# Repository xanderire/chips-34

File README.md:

# chips-34

Prototype, diodless pcb with minor key stagger and two thumb keys.

This started as a project to learn [Ergogen](https://github.com/ergogen/ergogen) and [KiCad](https://www.kicad.org/)

- Work-in-progress pcb that is under **100mm x 100mm** in order to facilitate a common discounted price for pcb manufactures for small pcbs.
- I do not claim this to be the most efficent or best way to build a keyboard pcb.
- This project is more to have fun and prototype different designs.
- As such I also cannot promise any files in this repo are correct and will work as production files.

---

## BOM

| Components                                              | Amount |
| :------------------------------------------------------ | :----: |
| Arduino Pro Micro                                       | 2      |
| TRRS-PJ-320A-dual                                       | 2      |
| SPST Tactile Switch                                     | 2      |
| Kailh MX Hotswap Sockets                                | 34     |
| MX Switches                                             | 34     |
| MX Keycaps                                              | 34     |

---

## Images

[(Back to top)](#chips-34)

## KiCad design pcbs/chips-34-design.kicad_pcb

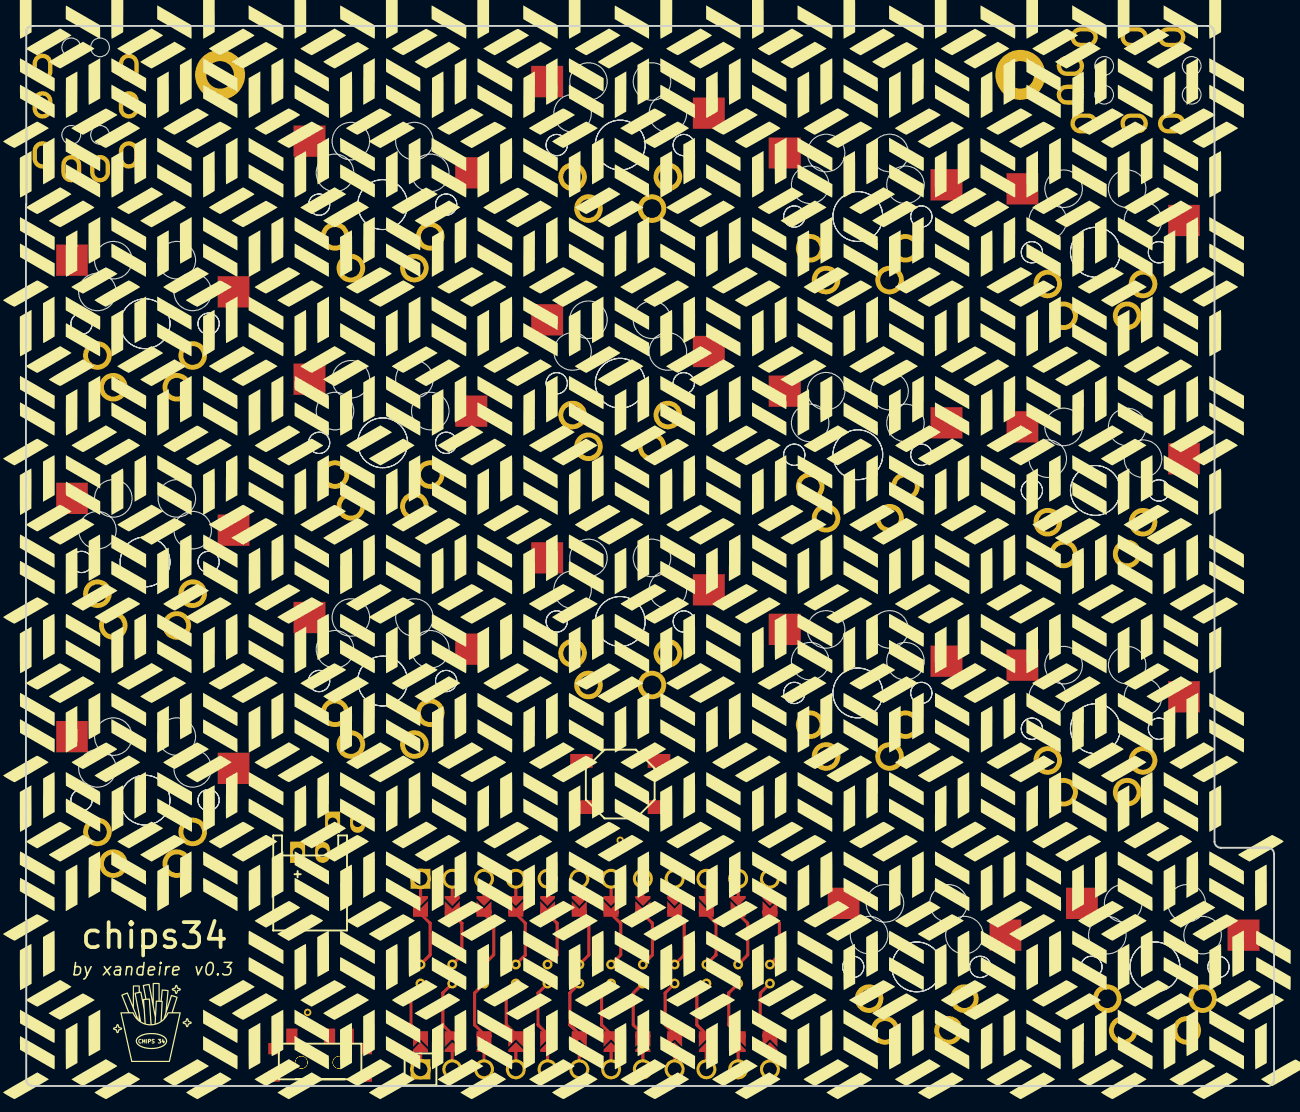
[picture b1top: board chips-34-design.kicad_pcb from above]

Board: 2 copper layers, 99.8 x 84.8 mm, 43 parts (0 on the bottom side), 23 nets, no tracks yet.

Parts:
B1, B2: SW_TACT_ALPS_SKQGABE010
JST1, JST2: JST_PH_S2B-PH-K_02x2.00mm_Angled
MCU1: ProMicro
S1, S2, S3, S4, S5, S6, S7, S8, S9, S10, S11, S12, S13, S14, S15, S16, S17, S18, S19, S20, S21, S22, S23, S24, S25, S26, S27, S28, S29, S30, S31, S32, S33, S34: MX
T1, T2: SPDT_C128955
TRRS1, TRRS2: TRRS-PJ-320A-dual

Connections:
BAT: JST1.1, JST2.1, T1.2, T2.2
GND: B1.2, B2.2, JST1.2, JST2.2, MCU1.2, MCU1.21, MCU1.22, S1.1, S2.1, S3.1, S4.1, S5.1, S6.1, S7.1, S8.1, S9.1, S10.1, S11.1, S12.1, S13.1, S14.1, S15.1, S16.1, S17.1, S18.1, S19.1, S20.1, S21.1, S22.1, S23.1, S24.1, S25.1, S26.1, S27.1, S28.1, S29.1, S30.1, S31.1, S32.1, S33.1, S34.1, TRRS1.1, TRRS1.2, TRRS2.1, TRRS2.2
P1: TRRS1.3, TRRS2.3
RAW: MCU1.1, T1.1, T2.1
RST: B1.1, B2.1, MCU1.3
VCC: MCU1.4, TRRS1.4, TRRS2.4
matrix_index_bottom: MCU1.16, S10.2, S27.2
matrix_index_home: MCU1.9, S11.2, S28.2
matrix_index_top: MCU1.8, S12.2, S29.2
matrix_inner_bottom: MCU1.14, S13.2, S30.2
matrix_inner_home: MCU1.15, S14.2, S31.2
matrix_inner_top: MCU1.10, S15.2, S32.2
matrix_middle_bottom: MCU1.17, S7.2, S24.2
matrix_middle_home: MCU1.7, S8.2, S25.2
matrix_middle_top: MCU1.18, S9.2, S26.2
matrix_pinky_bottom: MCU1.20, S1.2, S18.2
matrix_pinky_home: S2.2, S19.2
matrix_pinky_top: MCU1.23, MCU1.24, S3.2, S20.2
matrix_ring_bottom: MCU1.19, S4.2, S21.2
matrix_ring_home: MCU1.6, S5.2, S22.2
matrix_ring_top: MCU1.5, S6.2, S23.2
thumb_resting: MCU1.11, S16.2, S33.2
thumb_squeeze: MCU1.12, S17.2, S34.2

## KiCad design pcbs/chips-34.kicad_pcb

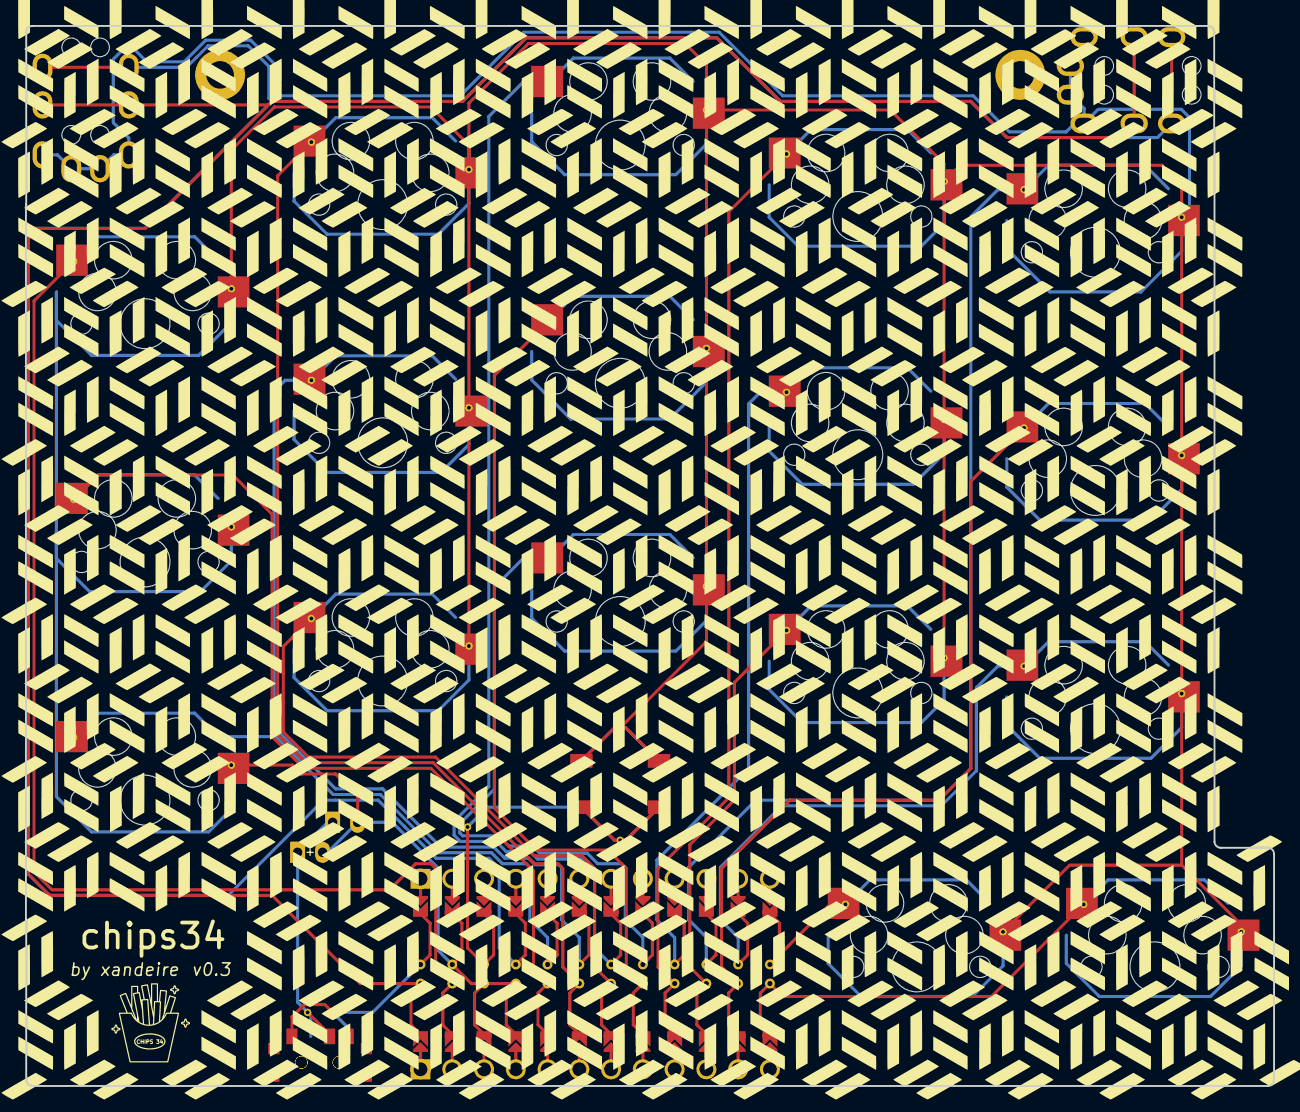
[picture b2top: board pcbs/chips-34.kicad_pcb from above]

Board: 2 copper layers, 99.8 x 84.8 mm, 26 parts (0 on the bottom side), 23 nets.

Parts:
B1, B2: SW_TACT_ALPS_SKQGABE010
JST1, JST2: JST_PH_S2B-PH-K_02x2.00mm_Angled
MCU1: ProMicro
S1, S2, S3, S4, S5, S6, S7, S8, S9, S10, S11, S12, S13, S14, S15, S16, S17: MX
T1, T2: SPDT_C128955
TRRS1, TRRS2: TRRS-PJ-320A-dual

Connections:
BAT: JST1.1, JST2.1, T1.2, T2.2
GND: B1.2, B2.2, JST1.2, JST2.2, MCU1.2, MCU1.21, MCU1.22, S1.1, S2.1, S3.1, S4.1, S5.1, S6.1, S7.1, S8.1, S9.1, S10.1, S11.1, S12.1, S13.1, S14.1, S15.1, S16.1, S17.1, TRRS1.1, TRRS1.2, TRRS2.1, TRRS2.2
P1: MCU1.24, TRRS1.3, TRRS2.3
RAW: MCU1.1, T1.1, T2.1
RST: B1.1, B2.1, MCU1.3
VCC: MCU1.4, TRRS1.4, TRRS2.4
matrix_index_bottom: MCU1.15, S10.2
matrix_index_home: MCU1.9, S11.2
matrix_index_top: MCU1.16, S12.2
matrix_inner_bottom: MCU1.11, S13.2
matrix_inner_home: MCU1.14, S14.2
matrix_inner_top: MCU1.10, S15.2
matrix_middle_bottom: MCU1.8, S7.2
matrix_middle_home: MCU1.17, S8.2
matrix_middle_top: MCU1.7, S9.2
matrix_pinky_bottom: MCU1.5, S1.2
matrix_pinky_home: MCU1.20, S2.2
matrix_pinky_top: MCU1.23, S3.2
matrix_ring_bottom: MCU1.18, S4.2
matrix_ring_home: MCU1.6, S5.2
matrix_ring_top: MCU1.19, S6.2
thumb_resting: MCU1.13, S16.2
thumb_squeeze: MCU1.12, S17.2

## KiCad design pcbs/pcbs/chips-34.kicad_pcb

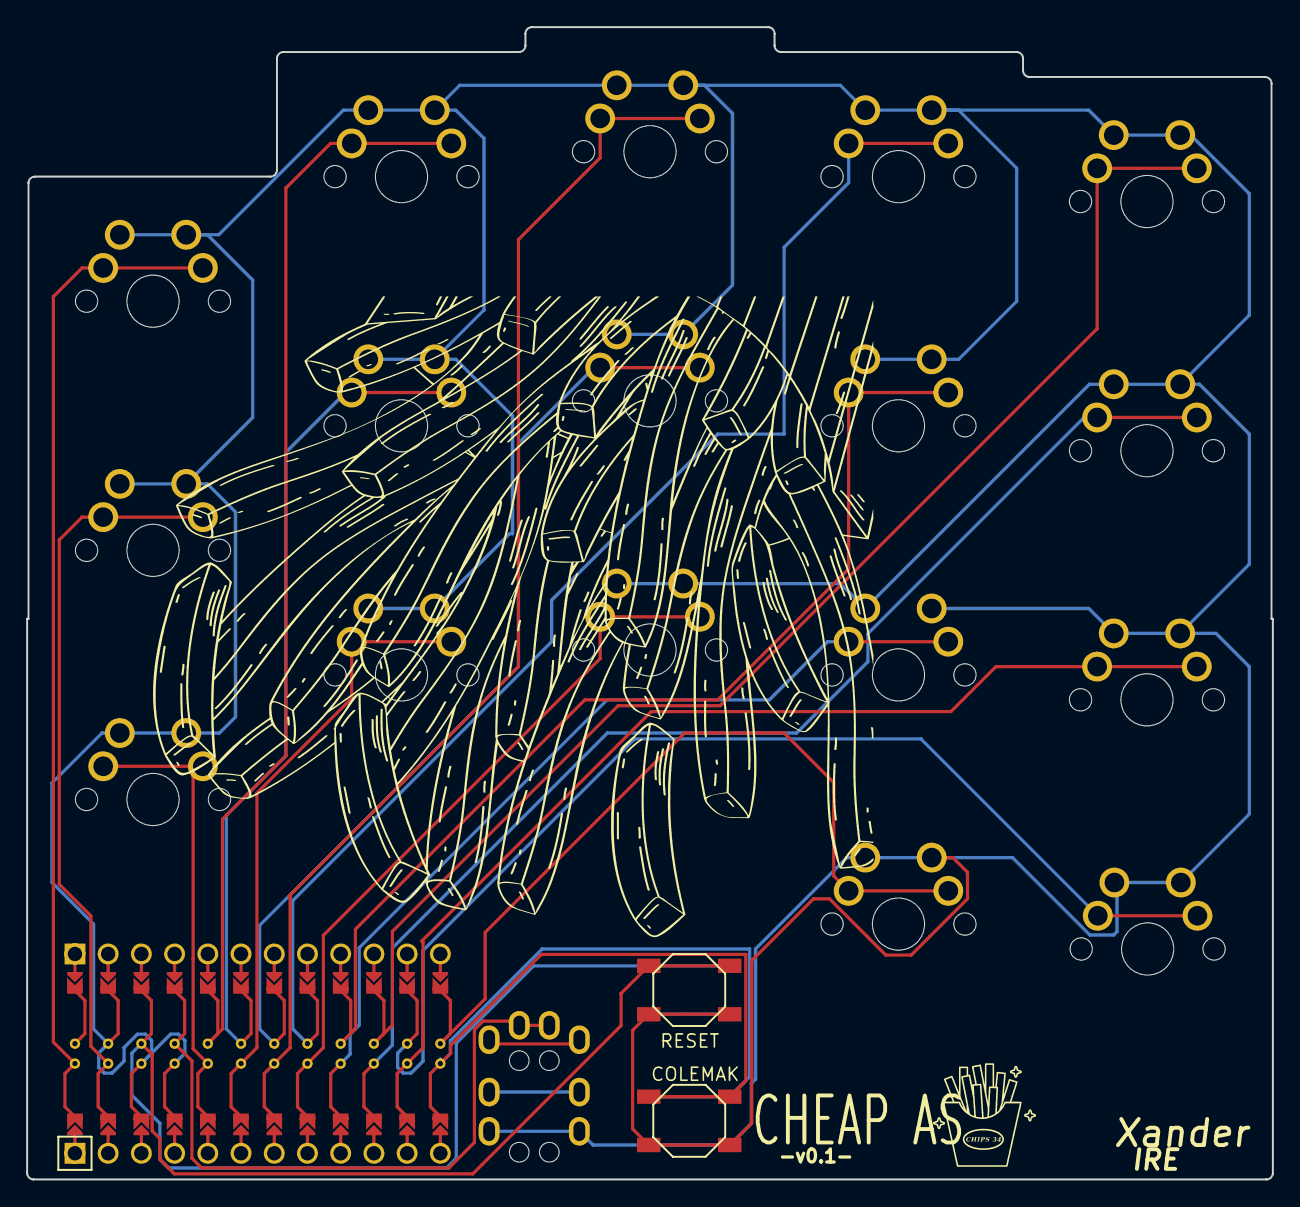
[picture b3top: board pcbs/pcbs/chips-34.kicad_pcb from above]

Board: 2 copper layers, 95.2 x 88.1 mm, 23 parts (0 on the bottom side), 21 nets.

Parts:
B1, B2, B3, B4: SW_TACT_ALPS_SKQGABE010
MCU1: ProMicro
S1, S2, S3, S4, S5, S6, S7, S8, S9, S10, S11, S12, S13, S14, S15, S16, S17: MX
TRRS1: TRRS-PJ-320A-dual

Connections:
GND: B1.2, B2.2, B3.2, B4.2, MCU1.2, MCU1.21, MCU1.22, S1.1, S2.1, S3.1, S4.1, S5.1, S6.1, S7.1, S8.1, S9.1, S10.1, S11.1, S12.1, S13.1, S14.1, S15.1, S16.1, S17.1, TRRS1.4
P9: B3.1, B4.1, MCU1.13
RST: B1.1, B2.1, MCU1.3
VCC: MCU1.4, TRRS1.1
matrix_index_bottom: MCU1.16, S10.2
matrix_index_home: MCU1.9, S11.2
matrix_index_top: MCU1.8, S12.2
matrix_inner_bottom: MCU1.14, S13.2
matrix_inner_home: MCU1.15, S14.2
matrix_inner_top: MCU1.10, S15.2
matrix_middle_bottom: MCU1.17, S7.2
matrix_middle_home: MCU1.7, S8.2
matrix_middle_top: MCU1.18, S9.2
matrix_pinky_bottom: MCU1.20, S1.2
matrix_pinky_home: MCU1.23, S2.2
matrix_pinky_top: MCU1.24, S3.2
matrix_ring_bottom: MCU1.19, S4.2
matrix_ring_home: MCU1.6, S5.2
matrix_ring_top: MCU1.5, S6.2
thumb_resting: MCU1.11, S16.2
thumb_stretch: MCU1.12, S17.2

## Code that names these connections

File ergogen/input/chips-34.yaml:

# diodless, cheap columnar pcb design with pinky stagger and two thumb keys

points:
  zones:
    matrix:
      columns:
        pinky:
        ring:
          key:
            stagger: 0.5U
        middle:
          key:
            stagger: 0.25U
        index:
          key:
            stagger: -0.3U
        inner:
          key:
            stagger: -0.15U
      rows:
        bottom:
          padding: 1U
        home:
          padding: 1U
        top:
          padding: 1U
    thumb:
      anchor:
        ref: matrix_inner_bottom
        shift: [0.25U, -1U]
        rotate: 0
      columns:
        resting:
          key:
            name: thumb_resting
        squeeze:
          key:
            name: thumb_squeeze
            spread: 1U
            splay: 0
            shift: [-2U, 0]
            rotate: 0

outlines:
  raw:
    - what: rectangle
      where: true
      asym: left
      size: [1U, 1U]
      corner:
    - what: rectangle
      where: thumb_squeeze
      size: [95, 1.9U]
      adjust:
        ref: matrix_middle_bottom
        shift: [0, -U]
    - what: rectangle
      where: thumb_resting
      size: [1U, U]
      adjust:
        shift: [-0.6, 0]
    - what: rectangle
      where: matrix_middle_top
      size: [95, 1U]
  panel:
    - what: outline
      name: raw
      fillet: 0.5
  switch_cutouts:
    - what: rectangle
      where: true
      asym: left
      size: 14
      bound: false
  switch_plate:
    main:
      what: outline
      name: panel
      fillet: 0.5
    keyholes:
      what: outline
      name: switch_cutouts
      operation: subtract
    mcu_cutout:
      what: polygon
      points:
        - ref: matrix_ring_bottom
          shift: [-0.5U, 0.5U]
        - ref: matrix_ring_bottom
          shift: [0.5U, 0.5U]
        - ref: matrix_middle_bottom
          shift: [-0.5U, 0.5U]
        - ref: matrix_middle_bottom
          shift: [0.5U, 0.5U]
        - ref: matrix_middle_bottom
          shift: [0.5U, 0.2U]
        - ref: matrix_index_bottom
          shift: [-0.25U, 0.5U]
        - ref: matrix_index_bottom
          shift: [-0.25U, -0.7U]
        - ref: matrix_pinky_bottom
          shift: [-0.5U, -0.5U]
        - ref: matrix_pinky_bottom
          shift: [-0.5U, 0.5U]
        - ref: matrix_pinky_bottom
          shift: [0.5U, 0.5U]
      adjust:
          shift: [0, -1U]
      operation: subtract
    trrs_up_cutout:
      what: rectangle
      where: matrix_pinky_top
      size: [0.5U, 1U]
      adjust:
        shift: [-0.25U, 1U]
      operation: subtract
    trrs_side_cutout:
      what: rectangle
      where: matrix_inner_top
      size: [1U, 0.5U]
      adjust:
        shift: [0.33U, 0.74U]
      operation: subtract
  preview:
    [panel]

pcbs:
  chips-34:
    outlines:
      board:
        outline: preview
      keycaps:
        outline: switch_cutouts
        layer: Eco1.User
    footprints:
      mx_hotswap:
        what: mx
        where: true
        params:
          from: GND
          to: "{{name}}"
          reverse: true
          keycaps: true
          hotswap: true
      mcu:
        what: promicro_pretty
        where:
          - ref: matrix_middle_bottom
            shift: [-2, -1.48U]
            rotate: 0
        params:
          P21: matrix_pinky_bottom
          P20: matrix_ring_home
          P19: matrix_middle_top
          P18: matrix_middle_bottom        
          P15: matrix_index_home
          P14: matrix_inner_top
          P16: matrix_inner_bottom
          P10: thumb_squeeze
          # P1:
          P0: matrix_pinky_top
          P2: matrix_pinky_home
          P3: matrix_ring_top
          P4: matrix_ring_bottom
          P5: matrix_middle_home
          P6: matrix_index_top
          P7: matrix_index_bottom
          P8: matrix_inner_home
          P9: thumb_resting
      via_switch_pin:
        what: via
        where: true
        params:
          net: "{{name}}"
        adjust:
          shift: [-5.7, 5]
      via_switch_gnd:
        what: via
        where: true
        params:
          net: GND
        adjust:
          shift: [6.9, 2.8]
      trrs_side:
        what: trrs
        where:
          ref: matrix_inner_top
          shift: [9.3, 12.6]
          rotate: -90
        params:
          mirror: true
          reverse: true
          symmetric: false
          A: GND
          B: GND
          C: P1
          D: VCC
      trrs_up:
        what: trrs
        where:
          ref: matrix_pinky_top
          shift: [-3.6, 23.7]
        params:
          mirror: true
          reverse: true
          symmetric: false
          A: GND
          B: GND
          C: P1
          D: VCC
      reset_button:
        what: button
        where:
          ref: matrix_middle_bottom
          shift: [0, -13]
          rotate: 180
        params:
          from: RST
          to: GND
          side: F
      reset_button_reverse:
        what: button
        where:
          ref: matrix_middle_bottom
          shift: [0, -13]
          rotate: 180
        params:
          from: RST
          to: GND
          side: B
      via_rst:
        what: via
        adjust: 
          ref: matrix_middle_bottom
          shift: [0, -17.5]
        params: 
          net: RST
      via_rst_gnd:
        what: via
        adjust: 
          ref: matrix_middle_bottom
          shift: [0, -8.5]
        params: 
          net: GND
      powerswitch_front:
        what: slider
        where:
          ref: matrix_ring_bottom
          rotate: 180
          shift: [-5, -30.5]
        params:
          from: RAW
          to: BAT
          side: F
      powerswitch_back:
        what: slider
        where:
          ref: matrix_ring_bottom
          rotate: 180
          shift: [-5, -30.5]
        params:
          from: RAW
          to: BAT
          side: B
      via_power_raw:
        what: via
        adjust: 
          ref: matrix_ring_bottom
          shift: [-4, -26.5]
        params: 
          net: RAW
      via_power_bat:
        what: via
        adjust: 
          ref: matrix_ring_bottom
          shift: [-6, -26.5]
        params: 
          net: BAT
      bat_front:
        what: jstph
        where:
          ref: matrix_ring_bottom
          shift: [-5.8, -13.7]
        params:
          pos: BAT
          neg: GND
          side: F
      bat_back:
        what: jstph
        where:
          ref: matrix_ring_bottom
          shift: [-3, -11.3]
        params:
          pos: BAT
          neg: GND
          side: B

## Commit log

2023-03-16 adding required ergogen files
2023-03-16 adding pcb files
2023-03-16 adding basic readme details
2023-03-16 updating readme links and formatting
2023-03-16 reorganising file structure
2023-03-16 adding image files for reference
2023-03-16 updating readme with bom and images
2023-03-16 adding temporary firmware files
2023-03-16 updating readme
2023-03-27 add mouse controls to keymap
2023-03-27 Reassign serial trrs conn to correct pin
2023-04-08 update ergogen yaml to new design
2023-04-08 update switch plate cutouts
2023-04-08 update outlines with component cutouts
2023-04-08 add updated gerbers for production
2023-04-08 reformat images for new ver .3
2023-04-08 correct img extension
2023-04-08 correct coord layout for v.3
2023-04-08 refactor qmk files
2023-04-08 remove extra kicad files
2023-04-08 remove old img files
2023-04-08 add premade firmware files for flashing mcu
2023-04-08 update readme BOM for new pcb
2023-04-21 fix reversed right hand mcu pin layout
2023-04-21 update firmware with reversed pins fix
